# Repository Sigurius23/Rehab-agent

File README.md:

# Rehab Agent — Meta-Repository

> A curated meta-repo that organises **117 upstream GitHub repositories** into one
> rehabilitation-technology pipeline: capture → pose → body/skeleton model →
> biomechanics → muscle simulation → feedback & visualisation.
>
> **This repo contains no upstream code.** It contains a machine-readable catalog,
> clone/status tooling, architecture docs, recommended stacks, and the first
> working pipeline slice (`pipeline/`: video → SKEL → OpenSim). Each upstream
> project stays in its own repo, under its own license.

## ⚠️ Not a medical device

Research and engineering use only. Nothing here diagnoses, treats, or replaces a
clinician. Any patient-facing use needs clinical validation, ethics approval, and
privacy review for video / IMU / health data. See
[`docs/safety-and-licensing.md`](docs/safety-and-licensing.md).

## 🎯 Design priority #1: anatomical accuracy

**Full accuracy of the human body in the twin is the key requirement.**
A webcam + SMPL-X gives a statistically average body that moves plausibly —
that is Tier C screening, not a twin. The target is **Tier A**: the patient's
own bones, joint centres/axes and muscle attachments from their MRI/CT,
tracked live against that personalised model, with a measured error budget
attached to every output. Tiers, targets, onboarding pipeline and red lines:
[`docs/accuracy.md`](docs/accuracy.md) · [`stacks/digital-twin.md`](stacks/digital-twin.md).

## 📷 Selected hardware

**RGB camera(s) + iPhone LiDAR (Pro, 12 Pro+) + optional RealSense D455.**
Roles, verified sensor specs, clinic-rig geometry, and the calibration/sync
protocol are fixed in [`docs/hardware.md`](docs/hardware.md). Honest summary:
LiDAR/D455 surfaces are centimetre-class (Tier B) — they register shape and
support live tracking, but bone/joint/muscle accuracy still comes from MRI/CT
(Tier A, `docs/accuracy.md`).

## 🧪 Working slice: video → SKEL → OpenSim

`pipeline/` (Python package `rehabtwin`) takes a front-end's 3D output (HSMR/SKEL, or
non-gated MediaPipe) and produces a scaled OpenSim model, joint angles, trunk/pelvis posture
against gravity, rep metrics, QC, a validation report and an HTML report. Every output is
labelled with its accuracy tier.

```bash
pip install -e "pipeline[test]" && python3 scripts/clone.py --only perfanalytics/pose2sim
cd pipeline && python -m rehabtwin selftest /tmp/rt     # synthetic squat with known truth: ~1° joint-angle RMSE
```

Measured so far ([`docs/validation-results.md`](docs/validation-results.md)): the back-end
recovers known kinematics to about 1° (trunk lean vs gravity 0.35°). On real video,
single-camera MediaPipe fails every gate against a 4-camera reference, so it is not the
answer. The next step is HSMR/SKEL on the public OpenCap LabValidation dataset against
marker mocap. A person model keeps one person's bones and measurements across sessions and setups
([`docs/person-model.md`](docs/person-model.md)). Details: [`pipeline/README.md`](pipeline/README.md) ·
[`stacks/video-skel-opensim.md`](stacks/video-skel-opensim.md).

## 🧈 Fat distribution (separate folder)

Models of the patient's **fat/adipose distribution** — a layer the surface
scan alone cannot see (fat + muscle + bone are summed in SMPL/LiDAR shape).
Kept separate from the main catalog as requested: measured models from
MRI/CT (TotalSegmentator tissue subtasks, vatsatseg, whole-body compartment
quantification → Tier A) vs shape/silhouette-predicted depots (Pseudo-DXA,
UK-Biobank silhouette model → Tier B, **estimate only**), plus paper-only and
closed reference models: [`fat-distribution/README.md`](fat-distribution/README.md).

## 👟 Shoe CAD capability map (separate folder)

From a foot scan to a last, sole and printable shoe: 20 shoe and last design tools rated on 26 features, as an
interactive page with its generator and a CSV. Ratings are from published vendor material, not hands-on testing:
[`shoe-cad-map/README.md`](shoe-cad-map/README.md).

## Quick start

```bash
git clone <this-repo> rehab-agent && cd rehab-agent

python3 scripts/validate_catalog.py     # check the catalog (136 repos)
python3 scripts/list.py --tier core     # see the recommended first wave
python3 scripts/clone.py --tier core --dry-run
python3 scripts/clone.py --tier core    # shallow-clone core repos into upstream/
python3 scripts/status.py               # what is cloned, at what commit
python3 scripts/list.py --search imu    # e.g. the IMU / wearable path
```

Clones land in `upstream/<owner>/<repo>/` and are **git-ignored** — this meta-repo
stays small and never redistributes upstream code or model weights.

## The pipeline

```mermaid
flowchart LR
  A[Capture\nFreeMoCap · OpenCap · IMU · RGB-D] --> B[Pose / mocap\nPose2Sim · TransPose/PIP · MAMMA]
  B --> C[Body model\nSMPL-X · SMPLify-X · MMHuman3D]
  C --> D[Skeleton\nSKEL · OSSO · HSMR · SKEL-CF]
  D --> E[Biomechanics\nOpenSim · AddBiomechanics · Pose2Sim]
  E --> F[Muscle sim / control\nMyoSuite · MyoSim · SCONE · PHC]
  F --> G[Assessment & feedback\njoint angles · ROM · gait · torques]
  G --> H[Visualisation\naitviewer-skel · OpenCap Viewer · Blender/MuSkeMo]
```

Full data-flow, formats and contracts: [`docs/architecture.md`](docs/architecture.md).

## Catalog

Source of truth: [`catalog/repos.json`](catalog/repos.json) ·
Human views: [`docs/catalog.md`](docs/catalog.md) · [`catalog/repos.csv`](catalog/repos.csv) · [`catalog/repos.yaml`](catalog/repos.yaml)

### By category

| Category | What it covers | Repos |
|---|---|---:|
| `body-models` | Parametric body & skeleton models (SMPL/SMPL-X, SKEL, OSSO, tissues) | 10 |
| `anatomy-models` | Anatomy & personalised model generation | 7 |
| `pose-mocap` | Pose estimation & motion capture (video, markerless, IMU) | 23 |
| `biomechanics` | Biomechanics engines & OpenSim pipeline | 13 |
| `musculoskeletal-sim` | Musculoskeletal simulation, humanoid control & RL | 12 |
| `visualization-tools` | Visualization, viewers & editing tools | 8 |
| `data-capture` | RGB-D / sensor capture | 8 |
| `datasets-interaction` | Datasets & human-object/scene interaction | 2 |
| `rehab-assessment` | Rehab exercise assessment, clinical scores & movement correction | 3 |
| `haptics-exoskeleton` | Haptic feedback suits, exoskeleton hardware & actuators | 6 |
| `medical-imaging` | Medical imaging, segmentation & patient-specific anatomy (DICOM/MRI/CT) | 4 |
| `rehab-assistive` | Rehab, gait & assistive-device specific projects | 5 |
| `3d-reconstruction` | 3D reconstruction, mesh generation & world models | 9 |

### By tier

| Tier | Meaning | Repos |
|---|---|---:|
| `core` | Core — evaluate first for Rehab Agent v1 | 35 |
| `extended` | Extended — useful second wave / alternatives | 33 |
| `specialized` | Specialized — niche modality, task, or platform | 30 |
| `experimental` | Experimental — recent/paper code; validate before depending on it | 11 |
| `needs-review` | Needs review — source list gave no usable description | 0 (all resolved 2026-10-21) |
| `private` | Private — listed but not publicly cloneable | 1 |

### Core stack — evaluate first (35 repos)

| Repository | Category | Why it is core |
|---|---|---|
| [vchoutas/smplx](https://github.com/vchoutas/smplx) | body-models | SMPL-X: expressive parametric human body model (body, hands, face) |
| [MarilynKeller/OSSO](https://github.com/MarilynKeller/OSSO) | body-models | From a body shape, infer the anatomic skeleton |
| [MarilynKeller/SKEL](https://github.com/MarilynKeller/SKEL) | body-models | SKEL — From Skin to Skeleton: biomechanically accurate 3D digital humans (SIGGRAPH Asia 2023) |
| [opencap-org/opencap-core](https://github.com/opencap-org/opencap-core) | pose-mocap | Main OpenCap processing pipeline — markerless motion capture from smartphones |
| [opencap-org/opencap-processing](https://github.com/opencap-org/opencap-processing) | biomechanics | Utilities for processing OpenCap data |
| [MyoHub/myosuite](https://github.com/MyoHub/myosuite) | musculoskeletal-sim | MyoSuite — musculoskeletal environments/tasks in MuJoCo, wrapped in the Gym API |
| [MarilynKeller/SMPL2AddBiomechanics](https://github.com/MarilynKeller/SMPL2AddBiomechanics) | biomechanics | Enable inputting a SMPL sequence into AddBiomechanics to fit an OpenSim skeleton model to the sequence |
| [MarilynKeller/aitviewer-skel](https://github.com/MarilynKeller/aitviewer-skel) | visualization-tools | aitviewer fork supporting visualization of OpenSim models and SKEL |
| [MyoHub/myo_sim](https://github.com/MyoHub/myo_sim) | musculoskeletal-sim | Musculoskeletal models in MuJoCo |
| [MyoHub/myoconverter](https://github.com/MyoHub/myoconverter) | biomechanics | Convert OpenSim 4.0+ MSK models into MuJoCo format with optimized muscle kinematics and kinetics |
| [IsshikiHugh/HSMR](https://github.com/IsshikiHugh/HSMR) | pose-mocap | Reconstructing Humans with a Biomechanically Accurate Skeleton (CVPR 2025 Oral) |
| [opensim-org/opensim-core](https://github.com/opensim-org/opensim-core) | biomechanics | SimTK OpenSim C++ libraries and command-line applications, with Java/Python wrapping |
| [keenon/AddBiomechanics](https://github.com/keenon/AddBiomechanics) | biomechanics | A tool to automatically process and share biomechanics data |
| [perfanalytics/pose2sim](https://github.com/perfanalytics/pose2sim) | pose-mocap | Markerless kinematics with any cameras — from 2D pose estimation to 3D OpenSim motion |
| [vchoutas/smplify-x](https://github.com/vchoutas/smplify-x) | pose-mocap | Expressive Body Capture: 3D Hands, Face, and Body from a Single Image (SMPLify-X) |
| [eth-ait/aitviewer](https://github.com/eth-ait/aitviewer) | visualization-tools | A set of tools to visualize and interact with sequences of 3D data |
| [isl-org/Open3D](https://github.com/isl-org/Open3D) | 3d-reconstruction | Open3D: A Modern Library for 3D Data Processing |
| [Xinyu-Yi/TransPose](https://github.com/Xinyu-Yi/TransPose) | pose-mocap | TransPose — real-time motion capture that estimates poses and global translations using only 6 IMUs |
| [Xinyu-Yi/PIP](https://github.com/Xinyu-Yi/PIP) | pose-mocap | PIP — real-time system that captures physically correct human motion, joint torques, and ground reaction forces with only 6 IMUs |
| [freemocap/freemocap](https://github.com/freemocap/freemocap) | pose-mocap | FreeMoCap — Free Motion Capture for Everyone |
| [muelea/shapy](https://github.com/muelea/shapy) | body-models | Metric body-shape regression from an image (twin onboarding measurements) |
| [google-ai-edge/mediapipe](https://github.com/google-ai-edge/mediapipe) | pose-mocap | Real-time 33-landmark pose on phone/web/laptop |
| [open-mmlab/mmpose](https://github.com/open-mmlab/mmpose) | pose-mocap | RTMPose real-time pose toolbox (swappable 2D-pose layer) |
| [zju3dv/GVHMR](https://github.com/zju3dv/GVHMR) | pose-mocap | World/gravity-grounded SMPL motion from monocular video |
| [SlimeVR/SlimeVR-Server](https://github.com/SlimeVR/SlimeVR-Server) | data-capture | IMU full-body tracking server (wearable twin sensing) |
| [SlimeVR/SlimeVR-Tracker-ESP](https://github.com/SlimeVR/SlimeVR-Tracker-ESP) | data-capture | ESP32 IMU tracker firmware (open-hardware suit sensors) |
| [sccn/labstreaminglayer](https://github.com/sccn/labstreaminglayer) | data-capture | LSL: time-sync for video + IMU + EMG + haptics |
| [fokhruli/STGCN-rehab](https://github.com/fokhruli/STGCN-rehab) | rehab-assessment | Clinician-scored exercise quality (KIMORE / UI-PRMD) |
| [CEINMS/CEINMS](https://github.com/CEINMS/CEINMS) | biomechanics | EMG-informed, per-person calibrated muscle forces |
| [naubiomech/OpenExo](https://github.com/naubiomech/OpenExo) | haptics-exoskeleton | Modular open-source exoskeleton platform (hardware + control) |
| [senseshift/senseshift-firmware](https://github.com/senseshift/senseshift-firmware) | haptics-exoskeleton | DIY haptic vest/sleeve firmware (posture cueing suit) |
| [wasserth/TotalSegmentator](https://github.com/wasserth/TotalSegmentator) | medical-imaging | >100 anatomical structures segmented from the patient's own CT/MRI |
| [Slicer/Slicer](https://github.com/Slicer/Slicer) | medical-imaging | 3D Slicer: clinician DICOM/segmentation review — the accuracy gate |
| [realsenseai/librealsense](https://github.com/realsenseai/librealsense) | data-capture | RealSense SDK for the optional D455 depth camera (selected hardware) |
| [utahmobl/opencap-monocular](https://github.com/utahmobl/opencap-monocular) | pose-mocap | Single-phone video → OpenSim; 4.8° MAE vs marker mocap (preprint) — the monocular bar to beat |

## Recommended stacks

| Stack | Use when | Doc |
|---|---|---|
| Markerless video rehab | Patient exercises filmed on webcams/phones | [`stacks/markerless-video.md`](stacks/markerless-video.md) |
| IMU real-time home rehab | No cameras; 6-IMU wearables, live feedback | [`stacks/imu-realtime.md`](stacks/imu-realtime.md) |
| SMPL → biomechanics | You have SMPL/SMPL-X motion and need joint loads | [`stacks/smpl-to-biomechanics.md`](stacks/smpl-to-biomechanics.md) |
| Muscle simulation & RL | Simulate muscle effort, assistance, exoskeletons | [`stacks/muscle-sim-rl.md`](stacks/muscle-sim-rl.md) |
| Blender anatomy visualisation | Clinician/patient-facing 3D anatomy | [`stacks/blender-anatomy.md`](stacks/blender-anatomy.md) |
| Accuracy-first digital twin | Tier-A: patient MRI/CT → own bones/joints/muscles → live 1:1 tracking → wrong-vs-corrected view | [`stacks/digital-twin.md`](stacks/digital-twin.md) |
| Haptic suit + exoskeleton | Vibrotactile posture cueing now; powered joint support as research track | [`stacks/haptic-exo-suit.md`](stacks/haptic-exo-suit.md) |
| **Video → SKEL → OpenSim (implemented)** | One video (or several) → scaled OpenSim model, joint angles, posture vs gravity, validation | [`stacks/video-skel-opensim.md`](stacks/video-skel-opensim.md) |

## Repo map

```
rehab-agent/
├── README.md                  ← you are here
├── catalog/
│   ├── repos.json             ← SOURCE OF TRUTH (edit this)
│   ├── repos.csv / repos.yaml ← generated
├── docs/
│   ├── catalog.md             ← generated full tables (all 136)
│   ├── architecture.md        ← pipeline, data formats, contracts
│   ├── roadmap.md             ← phased build plan
│   ├── evaluation.md          ← scoring rubric for picking repos
│   ├── validation-results.md  ← what has actually been measured
│   └── safety-and-licensing.md
├── stacks/                    ← 8 opinionated recipes (video-skel-opensim is implemented)
├── pipeline/                  ← rehabtwin: video → SKEL → OpenSim slice (code, configs, tests)
│   ├── rehabtwin/             ← frames, filtering, OpenSim stage, metrics, validation, records, report
│   ├── adapters/              ← HSMR → SKEL sequence, MediaPipe extraction
│   ├── configs/               ← model/marker-set configs, exercise profiles
│   └── tests/                 ← unit + end-to-end (synthetic truth) tests
├── scripts/
│   ├── clone.py  list.py  status.py
│   ├── validate_catalog.py  generate_catalog.py
└── upstream/                  ← your clones go here (git-ignored)
```

## Working rules

1. **Edit `catalog/repos.json`, then regenerate:** `python3 scripts/generate_catalog.py`
2. **Never commit upstream clones, model weights, or patient data** (see `.gitignore`).
3. **Check the upstream license before any use** — especially SMPL/SMPL-X/STAR/SUPR
   model weights, which are typically gated and non-commercial.
4. Pin upstream commits in your own experiment notes (`scripts/status.py` prints HEADs).

## Contributing

See [`CONTRIBUTING.md`](CONTRIBUTING.md). Adding a repo = one JSON entry + regenerate + validate.

## License

This meta-repo's own docs and scripts: MIT (see `LICENSE`).
Exception: the open hardware in [`hardware/sensor-sole/`](hardware/sensor-sole/) is licensed under
CERN-OHL-S-2.0 (see that folder's `LICENSE`).
**Upstream repositories and model weights keep their own licenses** — this repo
grants you no rights to them.

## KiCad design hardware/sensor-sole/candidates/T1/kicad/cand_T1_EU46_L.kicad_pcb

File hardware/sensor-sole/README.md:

<!-- SPDX-FileCopyrightText: 2026 Rehab Agent meta-repo contributors -->
<!-- SPDX-License-Identifier: CERN-OHL-S-2.0 -->
# Sensor sole

This is an open pressure-sensing sole for five-toe barefoot shoes. The generator can produce it for other EU
sizes, for a measured foot length and width, or from a person's foot landmarks. That is a generator
capability, not a demonstrated fit: four configurations have been generated and checked, and none has been
fitted in a shoe. A thin passive flex circuit with 16 sensing regions lies in the shoe; a small pod outside
the shoe reads it.

**Order of work (decided 2026-11-04): simulation first, then a 3D-printed prototype, then the flex circuit.** The
simulation model ([`SIMULATION.md`](SIMULATION.md)) and the printable parts ([`PRINTED.md`](PRINTED.md)) are
generated from the same design as the flex boards. Nothing has been printed or bought.

**Status: design only, not released for fabrication.** The layout, its generator and KiCad boards exist;
nothing has been fabricated or measured. Physical sensing, fit in the shoe and durability are untested. No
fabricator has confirmed the assumptions in [`FABRICATION.md`](FABRICATION.md). Check results per size and
side are in DESIGN.md, sections 5 and 11. See [`DESIGN.md`](DESIGN.md) for the design, its targets against
Moticon OpenGo, and the validation plan.

| File | What it is |
|---|---|
| `DESIGN.md` | Design specification: fit, layer stack, sensing, routing, scaling, pod, calibration, decisions |
| `sole_gen.py` | Generator: foot spec → outline with toe tabs, sensing regions, electrode combs, routed copper, tail, checks; exports SVG, DXF, JSON, a board file and previews |
| `sole_route.py` | Copper routing used by the generator: sense lines (B.Cu) as a planar tree, guided fine-grid pass, common net (F.Cu), vias, stubs |
| `kicad_export.py` | Board file → KiCad 7 board (`.kicad_pcb` + `.kicad_pro`, which holds the design rules); run with the Python that ships KiCad's `pcbnew` |
| `verify_board.py` | Checks a board before fabrication: DRC with the project rules, the region-to-contact map traced through the copper, contact numbering, coverlay openings, provenance; writes `.drc.rpt` and `.check.json` |
| `make_fab.sh` | Generator → KiCad → check → Gerbers and drill; writes no fabrication files if the check fails |
| `kicad/` | All eight checked boards (EU 37, EU 42, EU 46 and the synthetic personal example, right and left), each with project rules, DRC report and check result; EU 42 previews |
| `COMPARISON.md` | How the design compares with OpenGo and open insoles: documented features and measured performance kept apart; our figures are design goals |
| `VERIFICATION.md` | Verification and risk summary: scope, identity and maps, reproducibility, checker negative controls, quantified geometry risks, what needs the fabricator or physical tests |
| `channel_map.py` | Resolves a sole's printed ID to exactly one verified channel map, or refuses (plain Python) |
| `maps/` | Deployed channel maps, one per passing board, each tied to the board's design hash and file sha256 |
| `manifest.py` | Writes `kicad/MANIFEST.json`: all committed boards with IDs, hashes and provenance |
| `tests/` | `test_verify_drc.py` and `test_verify_negative.py` (checker, KiCad's Python); `test_channel_map.py` (resolver, in CI); `test_generator_regressions.py` (fail-closed splitting, valid export outlines, the EU 37 routing regression); `test_sim_print.py` (simulation export and readout, printed parts); `test_sim_osim.py` (the sole on two- and multi-segment OpenSim feet, negative controls; the pipeline's Python); `test_dhondt_port.py` (port against the original equations); `test_foot_comparison.py` (comparison harness, Synergy checks); `test_case_store.py` (resumable case folders, standard library); `test_compare_results.py` (results checker, negative controls; standard library); `test_double_support.py` (double support and the quasi-static frame rule on kinematics alone, resumable parallel runs); `test_opencap_contacts.py` (OpenCap's contact-sphere rule, negative controls); `test_static_ik.py` (the static-IK setup builder: settings kept, paths replaced, unknown elements refused); `test_forceplate_metrics.py` (the force-plate metrics, the post-hoc coverage rule and the sideways diagnostic on synthetic frames); `test_dynamic.py` (the squat window, the dynamic metrics, the pilot gate, the settings log against the code, and amendment 5's validity, penetration and reporting; synthetic data, plus the recorded v1 pilot solution when present); `run_suites.py` (runs suites and records each test's outcome) |
| `FABRICATION.md` | Fabrication assumptions against published flex-PCB capabilities, open questions, draft enquiry (not sent) |
| `CANDIDATES.md` | Higher-resolution candidates, design and analysis only: the targeted candidate T1 beside the 16-region baseline, compared with a dense matrix; open-line diagnostics; crosstalk |
| `sole_candidate.py` | Builds a candidate from a layout file with the shared generator, rules and checker, and no code of its own |
| `candidates/` | T1's layout, boards, check results and maps (kept apart from the baseline's); `study.py` (baseline, T1 and matrix on the same outlines) and `open_line.py` (capacitance estimates) |
| `SIMULATION.md` | The sole in simulation: a sensorised contact layer in the OpenSim model, per-region readout, the first drop test, limits and next steps (including HPC) |
| `sole_sim.py` | Exports a sole for simulation, adds it to an OpenSim model, and reads simulated forces out per region in the pod's contact order (assumed sensor model) |
| `sim/` | Simulation exports of the current boards (`<id>.sole_sim.json`); `sim/spacing/` the EU 42 soles at 10, 7.5, 5, 3.75 and 2.5 mm contact spacing |
| `FOOT_MODELS.md` | Experimental controlled comparison of foot models on the same virtual sole, with one assumed (not measured) contact law and each model's native contact as a sensitivity analysis: adapter limits, D'Hondt port and its verification, results, discretisation sensitivity, Synergy kinematics; no model selected |
| `VALIDATION_PLAN.md` | Plan, not a result: force-plate comparison of the current foot-to-ground model first, then regional barefoot plantar pressure, then foot–insole contact; candidate public datasets and reference equipment. Stage A has started: OpenCap LabValidation's kinematics only (force data not opened); nothing bought or contacted |
| `TEST_RUNS.md` | Which tests ran and which skipped in each environment, and why (written by `tests/run_suites.py`) |
| `foot_models/` | `dhondt_port.py` (D'Hondt et al.'s passive foot laws in OpenSim, with the midtarsal moment table), `compare_feet.py` (quasi-static tasks), `run_comparison.py`, `synergy_kinematics.py`; `PROVENANCE.json` (hashes of every external model, function, source file, kinematics and sole, and of the port's output); `results_2026-11-04.json` (the 244 runs behind FOOT_MODELS.md); `case_store.py` (resumable, fingerprinted case folders); `compare_results.py` (checks a run's summary.json against the results file, case by case and field by field); `double_support.py` (quasi-static double support in a full measured posture, and the plan's quasi-static frame rule, for the force-plate check; resumable, parallel); `opencap_contacts.py` (foot contact spheres added to an OpenCap scaled model by OpenCap's own rule, for the force-plate check; checks itself against OpenCap's function); `static_ik.py` (inverse kinematics of a trial from its markers with another trial's settings: the quiet-standing trials, with the dataset's squat settings); `forceplate_frames_2026-11-06.json` (the force-plate check's phase 1, kinematics only: the quasi-static frames, the foot lengths, the models' registration and the solve's support check); `forceplate_metrics.py` and `results_forceplate_2026-11-06.json` (phase 2: the three metrics against the force plates, aggregate values only); `forceplate_posthoc.py` and `results_forceplate_posthoc_2026-11-06.json` (the owner's post-hoc plate-coverage and body-mass analysis, beside the pre-registered result); `forceplate_lateral.py` and `results_forceplate_lateral_posthoc_2026-11-06.json` (post-hoc diagnostic of the left/right share failure); `dynamic_track.py` (the dynamic comparison, amendment 4: the squat window, arm A's model, the two-arm MocoTrack and each solution's validity and tracking error; from settings v3, the trunk and arm actuators' strengths from inverse dynamics, with the check that no ground force reaches them, and the initial guess at each arm's contact balance; resumable, parallel), `dynamic_settings_log.json` (every settings version, why it changed and what judged it), `dynamic_solutions_2026-11-09.json` (the phase-1 record of the three pilots; the v3 pilot failed the gate and the stop rule closed the comparison), `dynamic_summary.py` (phase-1 record: every solve's validity under amendments 5 and 6, its pelvis residuals with the old and the body-weight limits, its contact penetration, and the pilot gate), `dynamic_metrics.py` (phase 2, against the plates, fixed before any solution; evaluated counts per arm and A minus B on trials evaluated in both, amendment 5) |
| `workstation/` | Setting up another machine (Linux or WSL2), such as the lab laptop: `setup.sh` (pinned environments, inputs fetched and checked against PROVENANCE.json, machine record, tests), `fetch_inputs.py`, `run_comparison.sh` (resumable, parallel; checks a full run's results); `run_dynamic.sh` (the dynamic comparison's phase 1, unattended in tmux: pilot, gate, then every solve; blocks sleep while it runs); `README.md` |
| `PRINTED.md` | The 3D-printed first prototype: TPU carrier with pockets, underside wire channels and a cover; proposed sensor stack; differences from the flex sole |
| `sole_print.py` | Builds the printed carrier and cover (STL) from a sole design, with printability and bed-fit checks |
| `print/` | Printable parts for EU 42 (carrier, cover, report, preview) |
| `compare_boards.py` | Compares two boards item by item (copper, outline, keep-outs, openings, contacts, identity, rules, maps) |
| `archive/` | Earlier verified board sets, kept unchanged for comparison |
| `person_example.json` | Personalisation format (illustrative values, not a real person) |
| `requirements.txt` | Python packages the generator needs |

```
pip install -r requirements.txt
python sole_gen.py --size 42 --out out/                  # EU 42, right foot (a few minutes: routing)
python sole_gen.py --size 42 --side L --out out/         # left foot
python sole_gen.py --foot person_example.json --out out/ # a person's foot
python3 kicad_export.py out/sole_EU42_R.board.json kicad/sole_EU42_R.kicad_pcb   # KiCad's Python
python3 verify_board.py kicad/sole_EU42_R.kicad_pcb                              # KiCad's Python
./make_fab.sh 42 R                                       # all of the above, then Gerbers if the check passes
```

## Licence

Everything in this folder is licensed under the **CERN Open Hardware Licence Version 2 – Strongly Reciprocal
(CERN-OHL-S-2.0)**; the full text is in [`LICENSE`](LICENSE). The rest of this repository remains under its own
licence (MIT; see the repository root).

Source Location: <https://github.com/Sigurius23/Rehab-agent/tree/main/hardware/sensor-sole>

If you make or convey a sole or pod built from this design, CERN-OHL-S-2.0 section 4 applies: give each
recipient the Complete Source or tell them this Source Location. This notice asks that the Source Location
be shown on the product's packaging or documentation.

This design is provided as is, without warranty (CERN-OHL-S-2.0 section 6). It is a research device. It is not a
medical device and is not validated for clinical use.

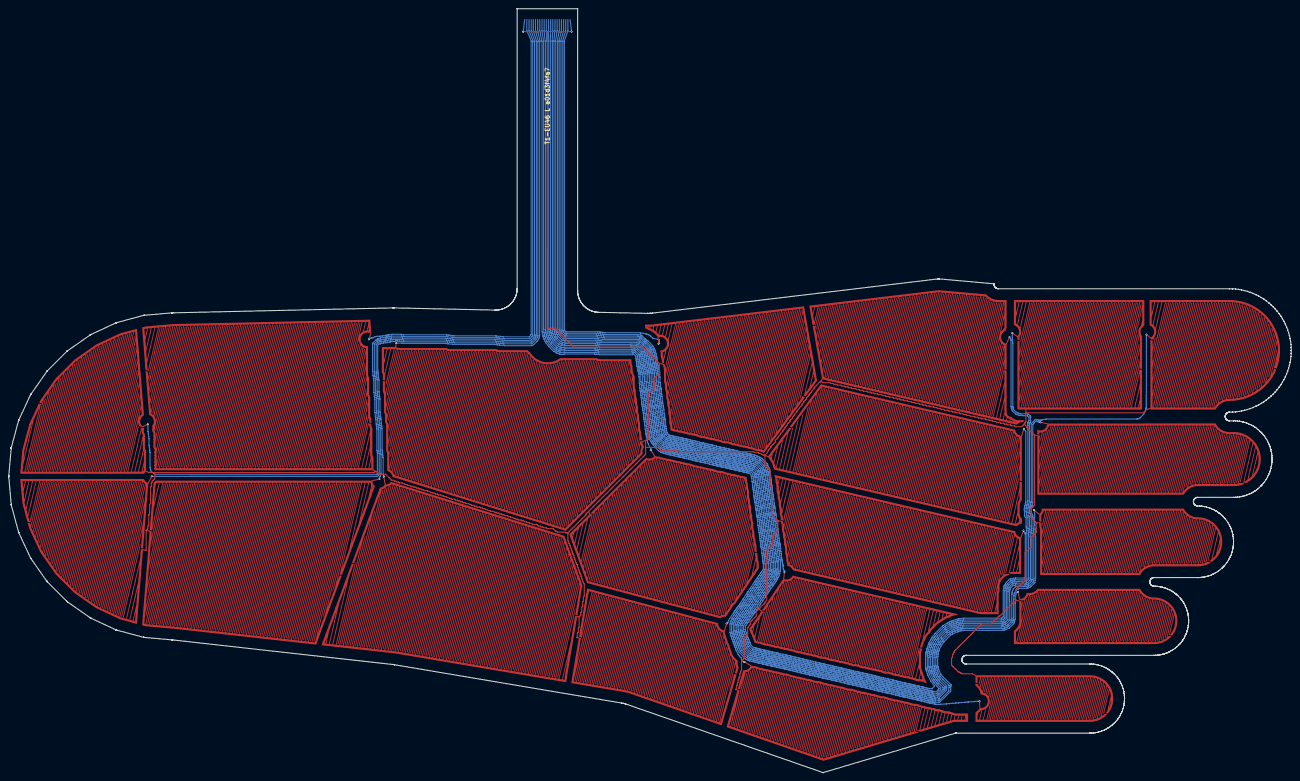
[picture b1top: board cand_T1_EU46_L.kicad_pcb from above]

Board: 2 copper layers, 296.8 x 176.8 mm, 21 parts (0 on the bottom side), 21 nets.

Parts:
J1: FFC 22p 0.5 mm, ZIF, stiffener to 0.3 mm total; ffc_contacts
S01: heel_pm; region
S02: heel_pl; region
S03: heel_am; region
S04: heel_al; region
S05: arch_med; region
S06: mid_lat_prox; region
S07: mid_lat_dist; region
S08: ffp_med; region
S09: ffp_cen; region
S10: mt1; region
S11: mt2; region
S12: mt3; region
S13: mt4; region
S14: mt5; region
S15: toe1_base; region
S16: toe1_tip; region
S17: toe2; region
S18: toe3; region
S19: toe4; region
S20: toe5; region

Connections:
COM: J1.1, J1.22, S01.2, S02.2, S03.2, S04.2, S05.2, S06.2, S07.2, S08.2, S09.2, S10.2, S11.2, S12.2, S13.2, S14.2, S15.2, S16.2, S17.2, S18.2, S19.2, S20.2
S_arch_med: J1.16, S05.1
S_ffp_cen: J1.15, S09.1
S_ffp_med: J1.2, S08.1
S_heel_al: J1.18, S04.1
S_heel_am: J1.21, S03.1
S_heel_pl: J1.19, S02.1
S_heel_pm: J1.20, S01.1
S_mid_lat_dist: J1.14, S07.1
S_mid_lat_prox: J1.17, S06.1
S_mt1: J1.6, S10.1
S_mt2: J1.5, S11.1
S_mt3: J1.4, S12.1
S_mt4: J1.3, S13.1
S_mt5: J1.13, S14.1
S_toe1_base: J1.7, S15.1
S_toe1_tip: J1.8, S16.1
S_toe2: J1.9, S17.1
S_toe3: J1.10, S18.1
S_toe4: J1.11, S19.1
S_toe5: J1.12, S20.1

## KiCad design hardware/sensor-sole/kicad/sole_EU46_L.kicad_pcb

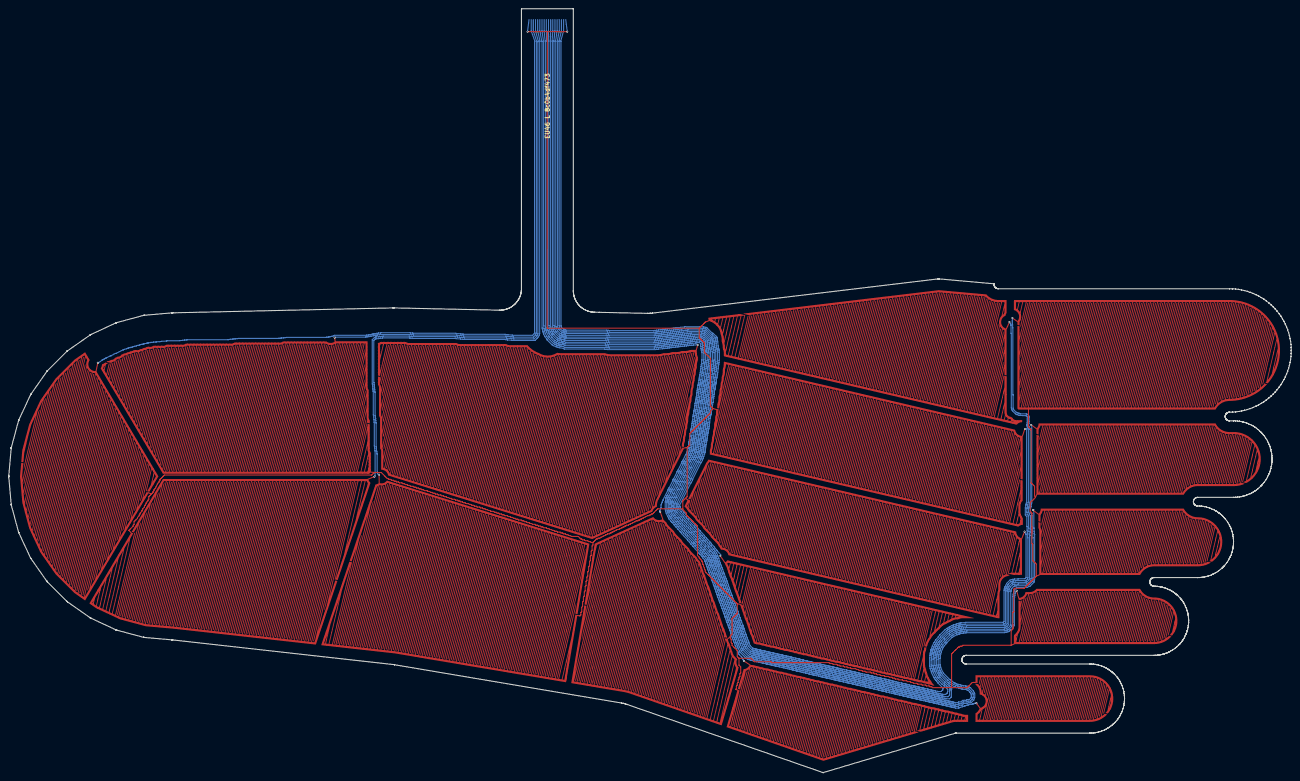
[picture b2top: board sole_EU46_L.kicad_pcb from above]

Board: 2 copper layers, 296.8 x 176.8 mm, 17 parts (0 on the bottom side), 17 nets.

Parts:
J1: FFC 18p 0.5 mm, ZIF, stiffener to 0.3 mm total; ffc_contacts
S01: heel_post; region
S02: heel_med; region
S03: heel_lat; region
S04: arch_med; region
S05: mid_lat_prox; region
S06: mid_lat_dist; region
S07: mt1; region
S08: mt2; region
S09: mt3; region
S10: mt4; region
S11: mt5; region
S12: toe1; region
S13: toe2; region
S14: toe3; region
S15: toe4; region
S16: toe5; region

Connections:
COM: J1.1, J1.18, S01.2, S02.2, S03.2, S04.2, S05.2, S06.2, S07.2, S08.2, S09.2, S10.2, S11.2, S12.2, S13.2, S14.2, S15.2, S16.2
S_arch_med: J1.13, S04.1
S_heel_lat: J1.15, S03.1
S_heel_med: J1.16, S02.1
S_heel_post: J1.17, S01.1
S_mid_lat_dist: J1.12, S06.1
S_mid_lat_prox: J1.14, S05.1
S_mt1: J1.5, S07.1
S_mt2: J1.4, S08.1
S_mt3: J1.3, S09.1
S_mt4: J1.2, S10.1
S_mt5: J1.11, S11.1
S_toe1: J1.6, S12.1
S_toe2: J1.7, S13.1
S_toe3: J1.8, S14.1
S_toe4: J1.9, S15.1
S_toe5: J1.10, S16.1

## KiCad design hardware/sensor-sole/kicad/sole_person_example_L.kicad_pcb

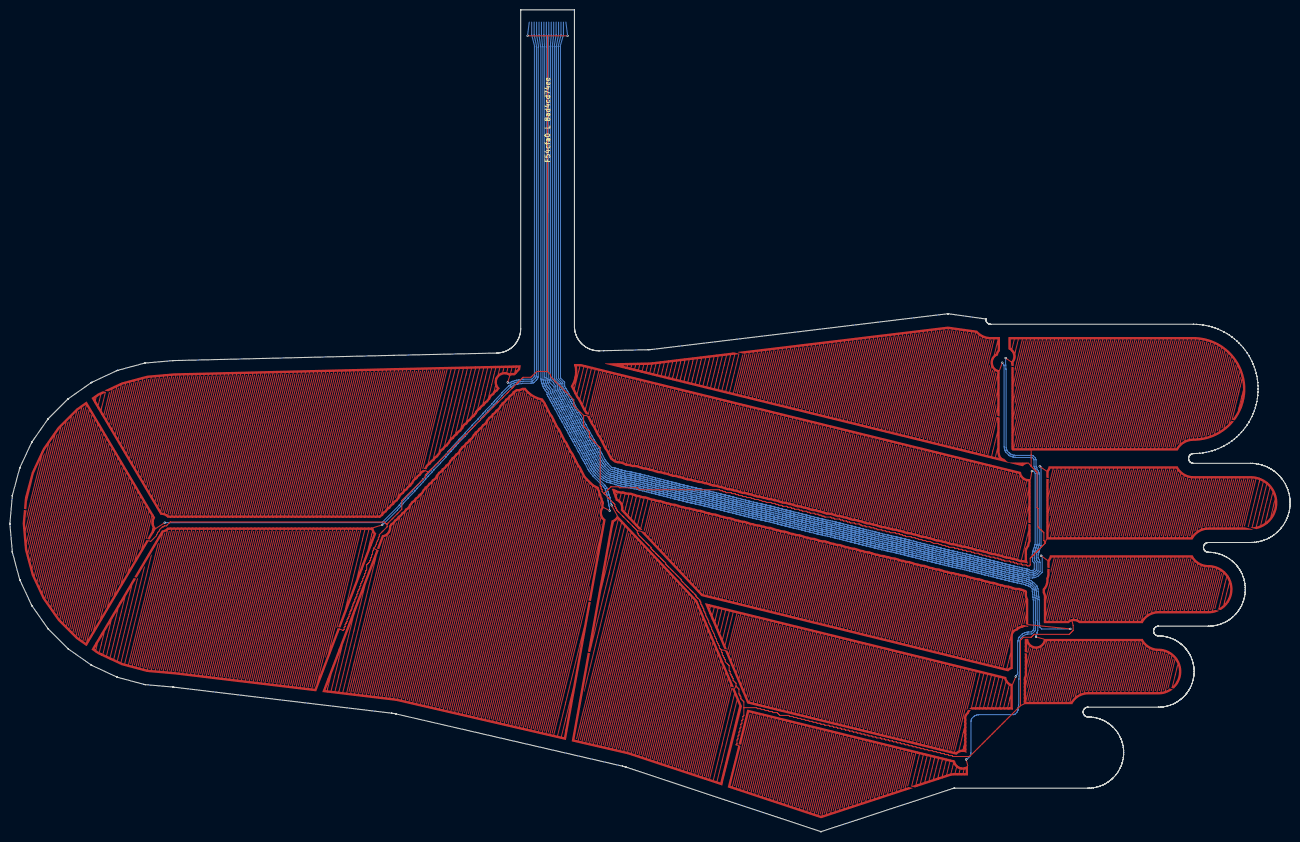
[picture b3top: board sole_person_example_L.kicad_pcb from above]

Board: 2 copper layers, 262.0 x 168.2 mm, 15 parts (0 on the bottom side), 15 nets.

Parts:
J1: FFC 16p 0.5 mm, ZIF, stiffener to 0.3 mm total; ffc_contacts
S01: heel_post; region
S02: heel_med; region
S03: heel_lat; region
S04: mid_lat_prox; region
S05: mid_lat_dist; region
S06: mt1; region
S07: mt2; region
S08: mt3; region
S09: mt4; region
S10: mt5; region
S11: toe1; region
S12: toe2; region
S13: toe3; region
S14: toe4; region

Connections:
COM: J1.1, J1.16, S01.2, S02.2, S03.2, S04.2, S05.2, S06.2, S07.2, S08.2, S09.2, S10.2, S11.2, S12.2, S13.2, S14.2
S_heel_lat: J1.13, S03.1
S_heel_med: J1.15, S02.1
S_heel_post: J1.14, S01.1
S_mid_lat_dist: J1.11, S05.1
S_mid_lat_prox: J1.12, S04.1
S_mt1: J1.3, S06.1
S_mt2: J1.2, S07.1
S_mt3: J1.7, S08.1
S_mt4: J1.10, S09.1
S_mt5: J1.9, S10.1
S_toe1: J1.4, S11.1
S_toe2: J1.5, S12.1
S_toe3: J1.6, S13.1
S_toe4: J1.8, S14.1

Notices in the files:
hardware/sensor-sole/candidates/T1/kicad/cand_T1_EU46_L.kicad_pcb:
CERN-OHL-S-2.0  Source: https://github.com/Sigurius23/Rehab-agent/tree/main/hardware/sensor-sole
